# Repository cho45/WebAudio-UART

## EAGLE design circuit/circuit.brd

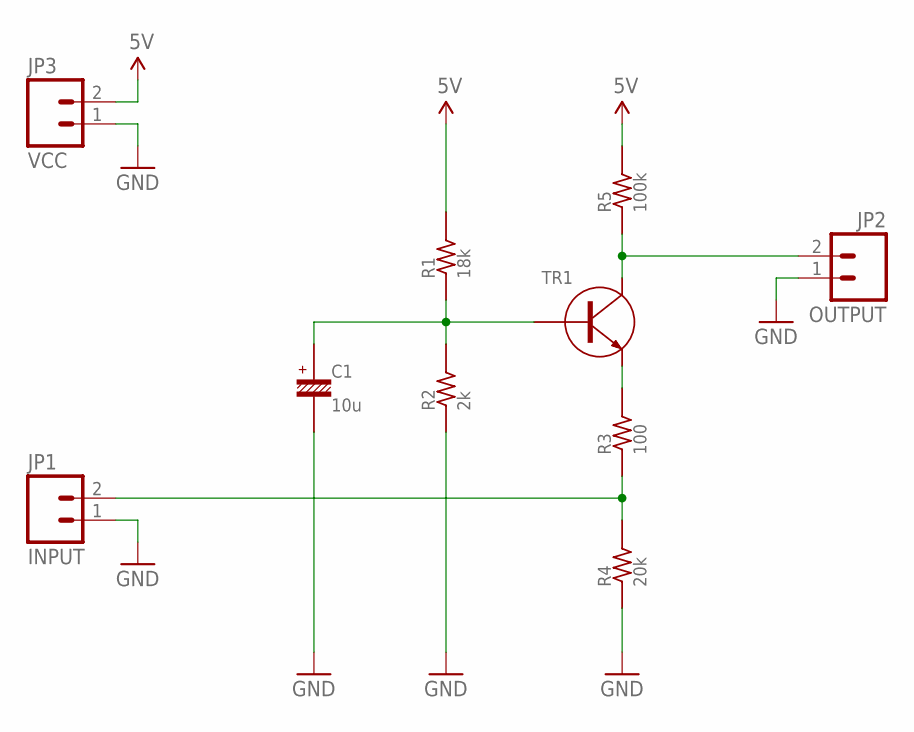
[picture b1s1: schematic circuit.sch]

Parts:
C1: 10u; 16V-4-2.54
JP1: INPUT; 1X02
JP2: OUTPUT; 1X02
JP3: VCC; 1X02
R1: 18k; 1/4W-7.62H
R2: 2k; 1/4W-7.62H
R3: 100; 1/4W-7.62H
R4: 20k; 1/4W-7.62H
R5: 100k; 1/4W-7.62H
TR1: TR-NPN-TO-92-ECB; TO-92

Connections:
5V: JP3.2, R1.PAD2 (2), R5.PAD2 (2)
GND: C1.-, JP1.1, JP2.1, JP3.1, R2.PAD1 (1), R4.PAD1 (1)
unnamed: JP2.2, R5.PAD1 (1), TR1.2 (C)
unnamed: R3.PAD2 (2), TR1.1 (E)
unnamed: JP1.2, R3.PAD1 (1), R4.PAD2 (2)
unnamed: C1.+, R1.PAD1 (1), R2.PAD2 (2), TR1.3 (B)

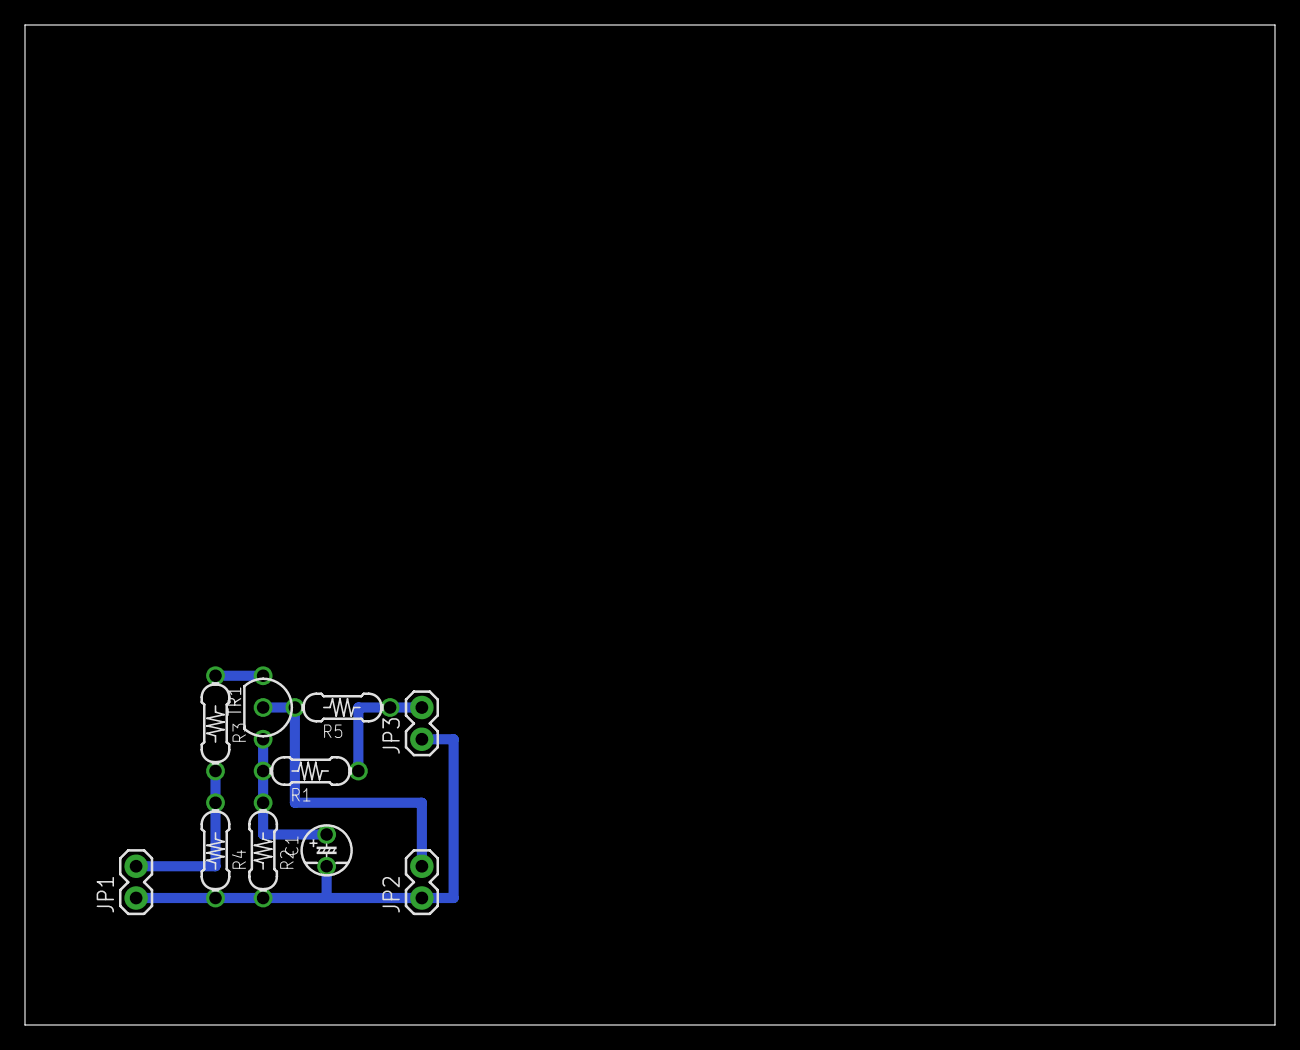
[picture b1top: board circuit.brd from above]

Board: 2 copper layers, 100.0 x 80.0 mm, 10 parts (0 on the bottom side), 6 nets.

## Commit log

2015-12-22 init

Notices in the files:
parts and their libraries:
SparkFun-Connectors: Licensing: CC v3.0 Share-Alike You are welcome to use this library for commercial purposes.
